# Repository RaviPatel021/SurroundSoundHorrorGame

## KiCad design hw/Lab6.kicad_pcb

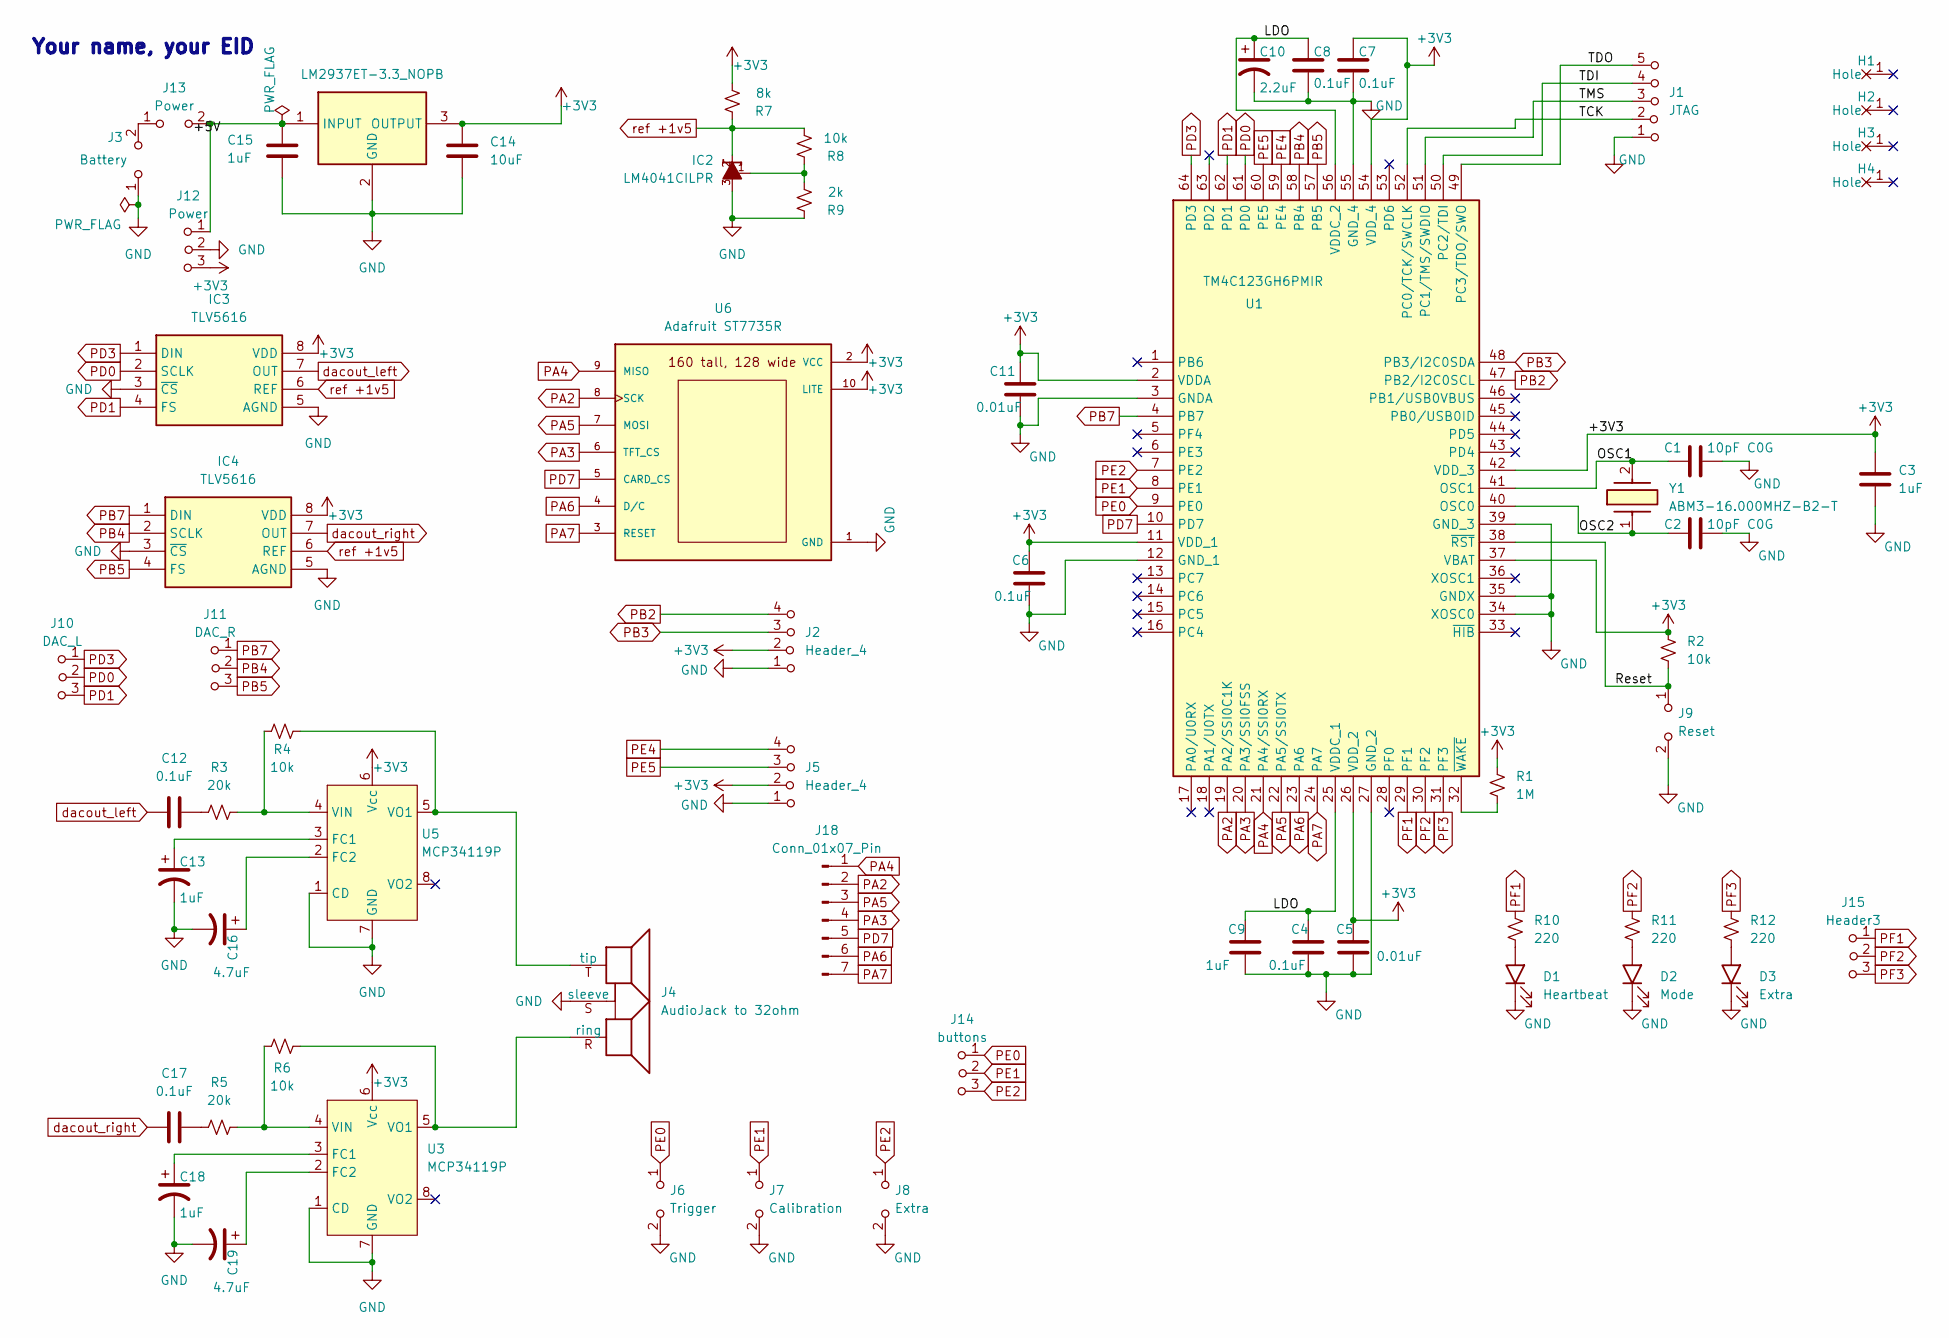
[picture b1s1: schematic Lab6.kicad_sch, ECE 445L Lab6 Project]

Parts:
C1, C2: 10pF C0G; C_Axial_200mil
C3, C9, C13, C15, C18: 1uF; C_Axial_200mil
C4, C6, C7, C8, C12, C17: 0.1uF; C_Axial_200mil
C5, C11: 0.01uF; C_Axial_200mil
C10: 2.2uF; C_Axial_200mil
C14: 10uF; C_Axial_200mil
C16, C19: 4.7uF; C_Axial_200mil
D1: Heartbeat; LED_D5.0mm
D2: Mode; LED_D5.0mm
D3: Extra; LED_D5.0mm
H1, H2, H3, H4: MountingHole_4_40
IC1: LM2937ET-3.3_NOPB; TO254P470X1028X1955-3P; Mouser Part Number 926-LM2937ET-3.3NOPB
IC2: LM4041CILPR; ti_LM4041CILPR
IC3, IC4: TLV5616; DIP-8_W7.62mm_LongPads
J1: JTAG; PinHeader_1x05_P2.54mm_Vertical
J2, J5: Header_4; PinHeader_1x04_P2.54mm_Vertical
J3: Battery; PinHeader_1x02_P2.54mm_Vertical
J4: AudioJack to 32ohm; Jack_3.5mm_CUI_SJ1-3523N_Horizontal
J6: Trigger; PinHeader_1x02_P2.54mm_Vertical
J7: Calibration; PinHeader_1x02_P2.54mm_Vertical
J8: Extra; PinHeader_1x02_P2.54mm_Vertical
J9: Reset; PinHeader_1x02_P2.54mm_Vertical
J10: DAC_L; PinHeader_1x03_P2.54mm_Vertical
J11: DAC_R; PinHeader_1x03_P2.54mm_Vertical
J12: Power; PinHeader_1x03_P2.54mm_Vertical
J13: Power; PinHeader_1x02_P2.54mm_Vertical
J14: buttons; PinHeader_1x03_P2.54mm_Vertical
J15: Header3; PinHeader_1x03_P2.54mm_Vertical
J18: Conn_01x07_Pin; PinHeader_1x07_P2.54mm_Vertical
R1: 1M; R_Axial_DIN0204_L3.6mm_D1.6mm_P5.08mm_Horizontal
R2, R4, R6, R8: 10k; R_Axial_DIN0204_L3.6mm_D1.6mm_P5.08mm_Horizontal
R3, R5: 20k; R_Axial_DIN0204_L3.6mm_D1.6mm_P5.08mm_Horizontal
R7: 8k; R_Axial_DIN0204_L3.6mm_D1.6mm_P5.08mm_Horizontal
R9: 2k; R_Axial_DIN0204_L3.6mm_D1.6mm_P5.08mm_Horizontal
R10, R11, R12: 220; R_Axial_DIN0204_L3.6mm_D1.6mm_P5.08mm_Horizontal
U1: TM4C123GH6PMIR; QFP50P1200X1200X160-64N; Mouser Part Number 595-TM4C123GH6PMIR
U3, U5: MCP34119P; DIP-8_W7.62mm_LongPads
U6: Adafruit ST7735R; adafruit_st7735r2
Y1: ABM3-16.000MHZ-B2-T; ABM3; Mouser Part Number 815-ABM3-16-B2-T

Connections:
+3V3: C3.1, C5.1, C6.1, C7.1, C11.1, C14.1, IC1.3 (OUTPUT), IC3.8 (VDD), IC4.8 (VDD), J2.2 (B), J5.2 (B), J12.3 (C), R1.1, R2.1, R7.2, U1.2 (VDDA), U1.11 (VDD_1), U1.26 (VDD_2), U1.37 (VBAT), U1.42 (VDD_3), U1.54 (VDD_4), U3.6 (Vcc), U5.6 (Vcc), U6.2 (VCC), U6.10 (LITE)
/+5V: C15.1, IC1.1 (INPUT), J12.1 (A), J13.2 (B)
/LDO: C4.1, C8.1, C9.1, C10.1, U1.25 (VDDC_1), U1.56 (VDDC_2)
/OSC1: C1.1, U1.41 (OSC1), Y1.2
/OSC2: C2.1, U1.40 (OSC0), Y1.1
/Reset: J9.1 (A), R2.2, U1.38 (~RST)
/TCK: J1.2 (B), U1.52 (PC0/TCK/SWCLK)
/TDI: J1.4 (C), U1.50 (PC2/TDI)
/TDO: J1.5 (C), U1.49 (PC3/TDO/SWO)
/TMS: J1.3 (C), U1.51 (PC1/TMS/SWDIO)
GND: C1.2, C2.2, C3.2, C4.2, C5.2, C6.2, C7.2, C8.2, C9.2, C10.2, C11.2, C13.2, C14.2, C15.2, C16.2, C18.2, C19.2, D1.1 (K), D2.1 (K), D3.1 (K), IC1.2 (GND), IC2.3, IC3.3 (~CS), IC3.5 (AGND), IC4.3 (~CS), IC4.5 (AGND), J1.1 (A), J2.1 (A), J3.1 (A), J4.S (sleeve), J5.1 (A), J6.2 (B), J7.2 (B), J8.2 (B), J9.2 (B), J12.2 (B), R9.1, U1.3 (GNDA), U1.12 (GND_1), U1.27 (GND_2), U1.34 (XOSC0), U1.35 (GNDX), U1.39 (GND_3), U1.55 (GND_4), U3.1 (CD), U3.7 (GND), U5.1 (CD), U5.7 (GND), U6.1 (GND)
unnamed: C12.2, R3.1
unnamed: C17.2, R5.1
unnamed: D1.2 (A), R10.2
unnamed: D2.2 (A), R11.2
unnamed: D3.2 (A), R12.2
unnamed: IC2.1, R8.1, R9.2
unnamed: J4.R (ring), R6.2, U3.5 (VO1)
unnamed: J4.T (tip), R4.2, U5.5 (VO1)
unnamed: J3.2 (B), J13.1 (A)
unnamed: R1.2, U1.32 (~WAKE)
unnamed: C18.1, U3.3 (FC1)
unnamed: C19.1, U3.2 (FC2)
unnamed: R5.2, R6.1, U3.4 (VIN)
unnamed: C13.1, U5.3 (FC1)
unnamed: C16.1, U5.2 (FC2)
unnamed: R3.2, R4.1, U5.4 (VIN)
PA2: J18.2, U1.19 (PA2/SSI0C1K), U6.8 (SCK)
PA3: J18.4, U1.20 (PA3/SSI0FSS), U6.6 (TFT_CS)
PA4: J18.1, U1.21 (PA4/SSI0RX), U6.9 (MISO)
PA5: J18.3, U1.22 (PA5/SSI0TX), U6.7 (MOSI)
PA6: J18.6, U1.23 (PA6), U6.4 (D/C)
PA7: J18.7, U1.24 (PA7), U6.3 (RESET)
PB2: J2.4 (C), U1.47 (PB2/I2C0SCL)
PB3: J2.3 (C), U1.48 (PB3/I2C0SDA)
PB4: IC4.2 (SCLK), J11.2 (B), U1.58 (PB4)
PB5: IC4.4 (FS), J11.3 (C), U1.57 (PB5)
PB7: IC4.1 (DIN), J11.1 (A), U1.4 (PB7)
PD0: IC3.2 (SCLK), J10.2 (B), U1.61 (PD0)
PD1: IC3.4 (FS), J10.3 (C), U1.62 (PD1)
PD3: IC3.1 (DIN), J10.1 (A), U1.64 (PD3)
PD7: J18.5, U1.10 (PD7), U6.5 (CARD_CS)
PE0: J6.1 (A), J14.1 (A), U1.9 (PE0)
PE1: J7.1 (A), J14.2 (B), U1.8 (PE1)
PE2: J8.1 (A), J14.3 (C), U1.7 (PE2)
PE4: J5.4 (C), U1.59 (PE4)
PE5: J5.3 (C), U1.60 (PE5)
PF1: J15.1 (A), R10.1, U1.29 (PF1)
PF2: J15.2 (B), R11.1, U1.30 (PF2)
PF3: J15.3 (C), R12.1, U1.31 (PF3)
dacout_left: C12.1, IC3.7 (OUT)
dacout_right: C17.1, IC4.7 (OUT)
ref +1v5: IC2.2, IC3.6 (REF), IC4.6 (REF), R7.1, R8.2

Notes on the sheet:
Your name, your EID

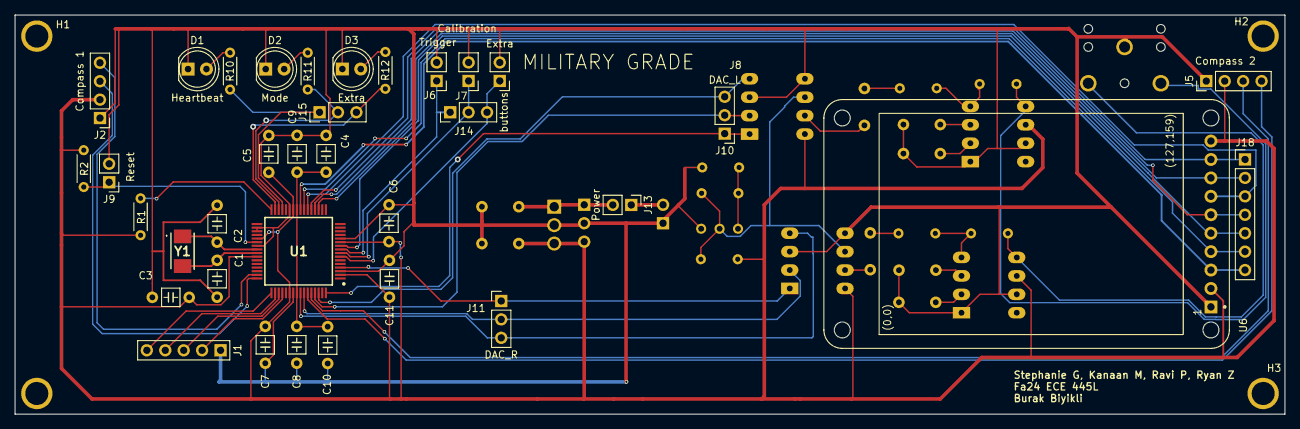
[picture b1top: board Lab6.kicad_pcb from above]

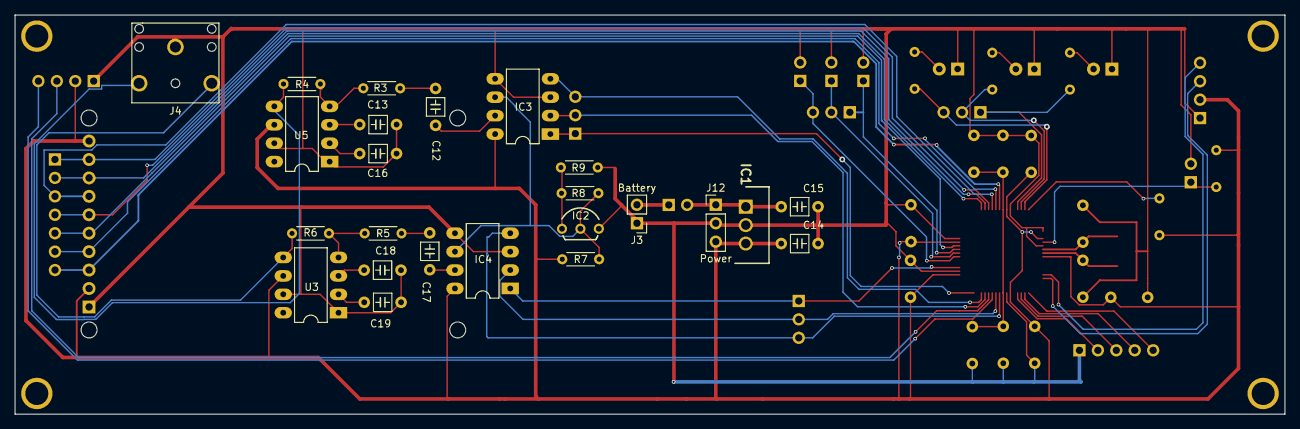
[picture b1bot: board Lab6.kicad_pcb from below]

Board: 2 copper layers, 175.0 x 55.0 mm, 63 parts (24 on the bottom side), 53 nets.

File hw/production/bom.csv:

Designator,Footprint,Quantity,Value,LCSC Part #
"C1, C2",C_Axial_200mil,2,10pF C0G,
C10,C_Axial_200mil,1,2.2uF,
"C11, C5",C_Axial_200mil,2,0.01uF,
"C12, C17, C4, C6, C7, C8",C_Axial_200mil,6,0.1uF,
"C13, C15, C18, C3, C9",C_Axial_200mil,5,1uF,
C14,C_Axial_200mil,1,10uF,
"C16, C19",C_Axial_200mil,2,4.7uF,
D1,LED_D5.0mm,1,Heartbeat,
D2,LED_D5.0mm,1,Mode,
D3,LED_D5.0mm,1,Extra,
"H1, H2, H3, H4",MountingHole_4_40,4,~,
IC1,TO254P470X1028X1955-3P,1,LM2937ET-3.3_NOPB,
IC2,ti_LM4041CILPR,1,LM4041CILPR,
"IC3, IC4",DIP-8_W7.62mm_LongPads,2,TLV5616,
J1,PinHeader_1x05_P2.54mm_Vertical,1,JTAG,
J10,PinHeader_1x03_P2.54mm_Vertical,1,DAC_L,
J11,PinHeader_1x03_P2.54mm_Vertical,1,DAC_R,
J12,PinHeader_1x03_P2.54mm_Vertical,1,Power,
J13,PinHeader_1x02_P2.54mm_Vertical,1,Power,
J14,PinHeader_1x03_P2.54mm_Vertical,1,buttons,
J15,PinHeader_1x03_P2.54mm_Vertical,1,Header3,
J18,PinHeader_1x07_P2.54mm_Vertical,1,Conn_01x07_Pin,
"J2, J5",PinHeader_1x04_P2.54mm_Vertical,2,Header_4,
J3,PinHeader_1x02_P2.54mm_Vertical,1,Battery,
J4,Jack_3.5mm_CUI_SJ1-3523N_Horizontal,1,AudioJack to 32ohm,
J6,PinHeader_1x02_P2.54mm_Vertical,1,Trigger,
J7,PinHeader_1x02_P2.54mm_Vertical,1,Calibration,
J8,PinHeader_1x02_P2.54mm_Vertical,1,Extra,
J9,PinHeader_1x02_P2.54mm_Vertical,1,Reset,
R1,R_Axial_DIN0204_L3.6mm_D1.6mm_P5.08mm_Horizontal,1,1M,
"R10, R11, R12",R_Axial_DIN0204_L3.6mm_D1.6mm_P5.08mm_Horizontal,3,220,
"R2, R4, R6, R8",R_Axial_DIN0204_L3.6mm_D1.6mm_P5.08mm_Horizontal,4,10k,
"R3, R5",R_Axial_DIN0204_L3.6mm_D1.6mm_P5.08mm_Horizontal,2,20k,
R7,R_Axial_DIN0204_L3.6mm_D1.6mm_P5.08mm_Horizontal,1,8k,
R9,R_Axial_DIN0204_L3.6mm_D1.6mm_P5.08mm_Horizontal,1,2k,
U1,QFP50P1200X1200X160-64N,1,TM4C123GH6PMIR,
"U3, U5",DIP-8_W7.62mm_LongPads,2,MCP34119P,
U6,adafruit_st7735r2,1,Adafruit ST7735R,
Y1,ABM3,1,ABM3-16.000MHZ-B2-T,

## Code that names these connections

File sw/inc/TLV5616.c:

// TLV5616.c
// Runs on TM4C123
// Use SSI1 to send a 16-bit code to the TLV5616 and return the reply.
// Daniel Valvano
// EE445L Fall 2015
//    Jonathan W. Valvano 9/22/15

/* This example accompanies the book
   "Embedded Systems: Real Time Interfacing to ARM Cortex M Microcontrollers",
   ISBN: 978-1463590154, Jonathan Valvano, copyright (c) 2014

 Copyright 2014 by Jonathan W. Valvano, valvano@mail.utexas.edu
    You may use, edit, run or distribute this file
    as long as the above copyright notice remains
 THIS SOFTWARE IS PROVIDED "AS IS".  NO WARRANTIES, WHETHER EXPRESS, IMPLIED
 OR STATUTORY, INCLUDING, BUT NOT LIMITED TO, IMPLIED WARRANTIES OF
 MERCHANTABILITY AND FITNESS FOR A PARTICULAR PURPOSE APPLY TO THIS SOFTWARE.
 VALVANO SHALL NOT, IN ANY CIRCUMSTANCES, BE LIABLE FOR SPECIAL, INCIDENTAL,
 OR CONSEQUENTIAL DAMAGES, FOR ANY REASON WHATSOEVER.
 For more information about my classes, my research, and my books, see
 http://users.ece.utexas.edu/~valvano/
 */

// SSIClk (SCLK) connected to PD0
// SSIFss (FS)   connected to PD1
// SSITx (DIN)   connected to PD3

#include <stdint.h>
#include "../inc/tm4c123gh6pm.h"


//----------------   DAC_Init     -------------------------------------------
// Initialize TLV5616 12-bit DAC
// assumes bus clock is 80 MHz
// inputs: initial voltage output (0 to 4095)
// outputs:none

void DACInitLeft(uint16_t data);
void DACInitRight(uint16_t data);

void DAC_Init(uint16_t data){
	DACInitLeft(data);
	DACInitRight(data);
}

void DACInitLeft(uint16_t data) {
const uint32_t portd = 0x8;
	const uint32_t ssi3 = 0x8;
	const uint32_t pin0 = 0x1;
	const uint32_t pin1 = 0x2;
	const uint32_t pin2 = 0x4;
	const uint32_t pin3 = 0x8;
	const uint32_t pins = pin0 | pin1 | pin2 | pin3;
	// Consider the following registers:
	// SYSCTL_RCGCSSI_R, SSI3_CR1_R, SSI3_CPSR_R, SSI3_CR0_R, SSI3_DR_R, SSI3_CR1_R
	// PD0 SSI0Clk, PD1 SSI0Fss, PD2 SSI0Rx, PD3 SSI0Tx
	
	SYSCTL_RCGCSSI_R |= ssi3;
	
	SYSCTL_RCGCGPIO_R |= portd;
	while((SYSCTL_PRGPIO_R&portd) == 0){};
		
		GPIO_PORTD_AFSEL_R |= pins;
	GPIO_PORTD_PCTL_R = (GPIO_PORTD_PCTL_R&0xFFFF0000)+0x00001111; //assigns the SSI signals to the approporaite pins
	GPIO_PORTD_DIR_R |= (pin0|pin1|pin3);
	GPIO_PORTD_DEN_R |= pins;
	GPIO_PORTD_AMSEL_R = 0; // disable analog functionality on PA ... idt thsi is needed
		
	//now SSI3 initializations yippee
	SSI3_CR1_R = 0x00000000; //sets master mode (0), disables SSI
	SSI3_CR0_R &= ~(0x0000FFF0); // SCR = 0 SPO = 0 Freescale
	SSI3_CR0_R |= 0x80; // SPH = 1;
	SSI3_CR0_R |= 0x0F; // DSS = 16-bit data bc of how it works read the datasheet fuvckasses
	SSI3_CPSR_R = 0x04; // clock prescale divider = 4
	SSI3_DR_R = data; // load �data� into transmit FIFO
	SSI3_CR1_R |= 0x00000002; // enable SSI
}

void DACInitRight(uint16_t data) {
		const uint32_t portb = 0x2;
		const uint32_t pin4 = 0x10;
		const uint32_t pin5 = 0x20;
		const uint32_t pin6= 0x40;
		const uint32_t pin7 = 0x80;
		const uint32_t pins = pin4 | pin5 | pin6 | pin7;
		
	  // Consider the following registers:
	  // SYSCTL_RCGCSSI_R, SSI1_CR1_R, SSI1_CPSR_R, SSI1_CR0_R, SSI1_DR_R, SSI1_CR1_R
		
		SYSCTL_RCGCSSI_R |= 0x04; //setting up ssi module 2 yippee
		// PB4 SSI0Clk, PB5 SSI0Fss, PB6 SSI0Rx, PB7 SSI0Tx
		SYSCTL_RCGCGPIO_R |= portb;
		while((SYSCTL_PRGPIO_R&portb) == 0){}; //wait till porta is ready
		GPIO_PORTB_AFSEL_R |= pins; //pb4-7
		GPIO_PORTB_PCTL_R = (GPIO_PORTB_PCTL_R&0x000FFFF)+0x22220000; //assigns the SSI signals to the approporaite pins
		GPIO_PORTB_DIR_R |= (pin4 | pin5 | pin7);
		GPIO_PORTB_DEN_R |= pins; // digital enable pa2-5
		GPIO_PORTB_AMSEL_R = 0; // disable analog functionality on PA ... idt thsi is needed
		
		//now SSI0 initializations yippee
		SSI2_CR1_R = 0x00000000; //sets master mode (0), disables SSI
		SSI2_CR0_R &= ~(0x0000FFF0); // SCR = 0 SPO = 0 Freescale
		SSI2_CR0_R |= 0x80; // SPH = 1;
		SSI2_CR0_R |= 0x0F; // DSS = 16-bit data bc of how it works read the datasheet fuvckasses
		SSI2_CPSR_R = 0x04; // clock prescale divider = 4
		SSI2_DR_R = data; // load �data� into transmit FIFO
		SSI2_CR1_R |= 0x00000002; // enable SSI
}

// --------------     DAC_Out   --------------------------------------------
// Send data to TLV5616 12-bit DAC
// inputs:  voltage output (0 to 4095)
// 
void DAC_OutLeft(uint16_t code){
    // write this
    // Consider the following registers:
	  // SSI1_SR_R, SSI1_DR_R
		while((SSI3_SR_R&0x00000002)==0){};// SSI Transmit FIFO Not Full, waits for full
		SSI3_DR_R = code; //data out
		while((SSI3_SR_R&0x00000004)==0){};// SSI Receive FIFO Not Empty
		uint32_t receive = SSI3_DR_R; // acknowledge response 
}

void DAC_OutRight(uint16_t code){
    // write this
    // Consider the following registers:
	  // SSI1_SR_R, SSI1_DR_R
		while((SSI2_SR_R&0x00000002)==0){};// SSI Transmit FIFO Not Full, waits for full
		SSI2_DR_R = code; //data out
		while((SSI2_SR_R&0x00000004)==0){};// SSI Receive FIFO Not Empty
		uint32_t receive = SSI2_DR_R; // acknowledge response 
}

// --------------     DAC_OutNonBlocking   ------------------------------------
// Send data to TLV5616 12-bit DAC without checking for room in the FIFO
// inputs:  voltage output (0 to 4095)
// 
void DAC_Out_NB(uint16_t code){
    // Consider writing this (If it is what your heart desires)????
    // Consider the following registers:
	  // SSI1_SR_R, SSI1_DR_R
		while((SSI0_SR_R&0x00000002)==0){};// SSI Transmit FIFO Not Full
		SSI0_DR_R = code;
}

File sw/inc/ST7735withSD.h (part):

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// Runs on LM4F120/TM4C123
// Low level drivers for the ST7735 160x128 LCD based off of
// the file described above.  Further modified for simultaneous
// use of the SD card (CS on PD7) and ST7735 LCD (CS on PA3).
//    16-bit color, 128 wide by 160 high LCD
// Daniel Valvano
// Feb 22, 2016
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// **********ST7735 TFT and SDC*******************
// ST7735
// Backlight (pin 10) connected to +3.3 V
// MISO (pin 9) connected to PA4 (SSI0Rx)
// SCK (pin 8) connected to PA2 (SSI0Clk)
// MOSI (pin 7) connected to PA5 (SSI0Tx)
// TFT_CS (pin 6) connected to PA3 (GPIO/SSI0Fss)
// CARD_CS (pin 5) connected to PD7 or PB0 (GPIO)
// Data/Command (pin 4) connected to PA6 (GPIO), high for data, low for command
// RESET (pin 3) connected to PA7 (GPIO)
// VCC (pin 2) connected to +3.3 V
// Gnd (pin 1) connected to ground

// MISO (pin 9) connected to PA4 (SSI0Rx)
// SCK (pin 8) connected to PA2 (SSI0Clk)
// MOSI (pin 7) connected to PA5 (SSI0Tx)
// CARD_CS (pin 5) connected to PD7 or PB0 (GPIO)

// **********wide.hk ST7735R*******************
// Silkscreen Label (SDC side up; LCD side down) - Connection
// VCC  - +3.3 V
// GND  - Ground
// !SCL - PA2 Sclk SPI clock from microcontroller to TFT or SDC
// !SDA - PA5 MOSI SPI data from microcontroller to TFT or SDC
// DC   - PA6 TFT data/command
// RES  - PA7 TFT reset
// CS   - PA3 TFT_CS, active low to enable TFT
// *CS  - PD7 or PB0 SDC_CS, active low to enable SDC
// MISO - PA4 MISO SPI data from SDC to microcontroller
// SDA   (NC) I2C data for ADXL345 accelerometer
// SCL   (NC) I2C clock for ADXL345 accelerometer
// SDO   (NC) I2C alternate address for ADXL345 accelerometer
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

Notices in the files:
sw/inc/ST7735withSD.h:
MIT license, all text above must be included in any redistribution
